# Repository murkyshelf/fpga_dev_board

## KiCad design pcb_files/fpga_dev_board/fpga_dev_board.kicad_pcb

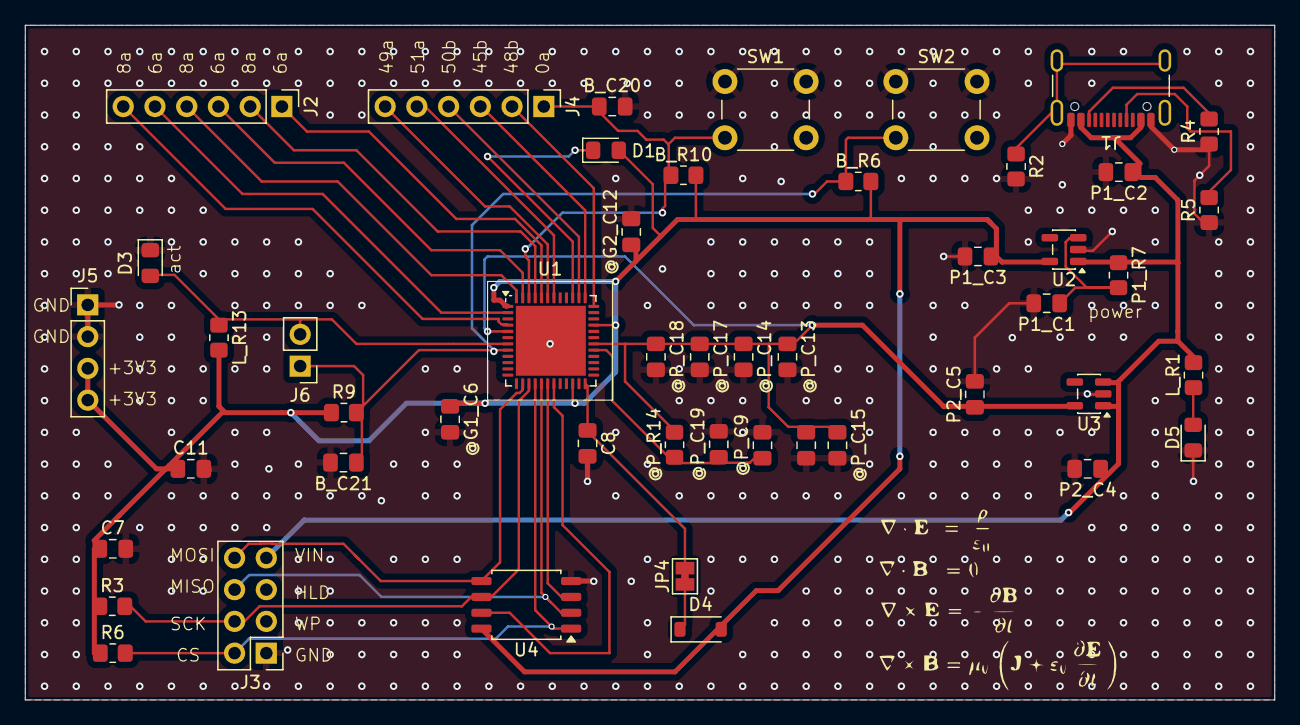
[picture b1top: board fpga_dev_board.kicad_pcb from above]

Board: 2 copper layers, 100.0 x 54.0 mm, 49 parts (0 on the bottom side), 33 nets.

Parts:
@G1_C6, @G2_C12: 100n; C_0805_2012Metric_Pad1.18x1.45mm_HandSolder
@P_C9, @P_C14, @P_C17: 100n; C_0805_2012Metric_Pad1.18x1.45mm_HandSolder
@P_C13, @P_C16: 10n; C_0805_2012Metric_Pad1.18x1.45mm_HandSolder
@P_C15, @P_C18: 1u; C_0805_2012Metric_Pad1.18x1.45mm_HandSolder
@P_C19: 10u; C_0805_2012Metric_Pad1.18x1.45mm_HandSolder
@P_R14: 100E; R_0805_2012Metric_Pad1.20x1.40mm_HandSolder
B_C20, B_C21: 1u; C_0805_2012Metric_Pad1.18x1.45mm_HandSolder
B_R6, B_R10: 10k; R_0805_2012Metric_Pad1.20x1.40mm_HandSolder
C7, C8, C11: 100n; C_0805_2012Metric_Pad1.18x1.45mm_HandSolder
D1: blue; LED_0805_2012Metric_Pad1.15x1.40mm_HandSolder
D3: green; LED_0805_2012Metric_Pad1.15x1.40mm_HandSolder
D4: 1N4148W; D_SOD-123
D5: red; LED_0805_2012Metric_Pad1.15x1.40mm_HandSolder
J1: USB_C; USB_C_Receptacle_GCT_USB4105-xx-A_16P_TopMnt_Horizontal
J2, J4: Conn_01x06; PinHeader_1x06_P2.54mm_Vertical
J3: spi programming; PinHeader_2x04_P2.54mm_Vertical
J5: Conn_01x04; PinHeader_1x04_P2.54mm_Vertical
J6: Conn_01x02; PinHeader_1x02_P2.54mm_Vertical
JP4: Jumper; SolderJumper-2_P1.3mm_Bridged_Pad1.0x1.5mm
L_R1, L_R13: 2k2; R_0805_2012Metric_Pad1.20x1.40mm_HandSolder
P1_C1: 1u; C_0805_2012Metric_Pad1.18x1.45mm_HandSolder
P1_C2, P1_C3, P2_C4, P2_C5: 4u7; C_0805_2012Metric_Pad1.18x1.45mm_HandSolder
P1_R7: 10k; R_0805_2012Metric_Pad1.20x1.40mm_HandSolder
R2: 1M; R_0805_2012Metric_Pad1.20x1.40mm_HandSolder
R3, R6, R9: 10k; R_0805_2012Metric_Pad1.20x1.40mm_HandSolder
R4, R5: 5k1; R_0805_2012Metric_Pad1.20x1.40mm_HandSolder
SW1, SW2: TACT; SW_PUSH_6mm_H5mm
U1: ICE40UP5K-SG48ITR; QFN-48-1EP_7x7mm_P0.5mm_EP5.6x5.6mm
U2, U3: TLV75533PDBV; SOT-23-5
U4: W25Q128JVS; SOIC-8_5.3x5.3mm_P1.27mm

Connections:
+1V2: @P_C13.1, @P_C14.1, @P_C15.1, @P_C16.1, @P_C17.1, @P_C18.1, @P_R14.2, P2_C5.1, U1.5 (VCC), U1.30 (VCC), U3.5 (OUT)
+3V3: @G1_C6.1, @G2_C12.1, B_R6.2, B_R10.2, C7.1, C11.1, D1.2 (A), D4.2 (A), J5.3, J5.4, L_R13.2, P1_C3.1, R3.1, R6.1, R9.1, U1.1 (VCCIO_2), U1.22 (SPI_VCCIO1), U1.33 (VCCIO_0), U2.5 (OUT), U4.8 (VCC)
/CDONE: D3.2 (A), J6.2, L_R13.1, U1.7 (CDONE)
/IOB_0a: B_C20.1, B_R10.1, J4.1, SW1.2, U1.46 (IOB_0a)
/IOB_2a: J2.3, U1.47 (IOB_2a)
/IOB_3a_G6: J2.1, U1.44 (IOB_3b_G6)
/IOB_4a: J2.4, U1.48 (IOB_4a)
/IOB_5a: J2.2, U1.45 (IOB_5b)
/IOB_6a: J2.5, U1.2 (IOB_6a)
/IOB_8a: J2.6, U1.4 (IOB_8a)
/IOT_45b: J4.3, U1.37 (IOT_45a_G1)
/IOT_48b: J4.2, U1.36 (IOT_48b)
/IOT_49a: J4.6, U1.43 (IOT_49a)
/IOT_50b: J4.4, U1.38 (IOT_50b)
/IOT_51a: J4.5, U1.42 (IOT_51a)
/SPI_MISO-IO1: J3.6, U1.17 (IOB_33b_SPI_SI), U4.2 (DO/IO_{1})
/SPI_MOSI-IO0: J3.8, U1.14 (IOB_32a_SPI_SO), U4.5 (DI/IO_{0})
/SPI_SCK: J3.4, R3.2, U1.15 (IOB_34a_SPI_SCK), U4.6 (CLK)
/SPI_~CS: J3.2, R6.2, U1.16 (IOB_35b_SPI_SS), U4.1 (~CS)
/SPI_~HLD-IO3: J3.3, U1.19 (IOB_29b), U4.7 (~HOLD/~RESET/IO_{3})
/SPI_~WP-IO2: J3.5, U1.18 (IOB_31b), U4.3 (~WP/IO_{2})
/led: D1.1 (K), U1.39 (RGB0)
/~BTN: B_C21.1, B_R6.1, J6.1, R9.2, SW2.2, U1.8 (~CRESET)
GND: @G1_C6.2, @G2_C12.2, @P_C9.2, @P_C13.2, @P_C14.2, @P_C15.2, @P_C16.2, @P_C17.2, @P_C18.2, @P_C19.2, B_C20.2, B_C21.2, C7.2, C8.2, C11.2, D3.1 (K), D5.1 (K), J1.A1 (GND), J1.A12 (GND), J1.B1 (GND), J1.B12 (GND), J3.1, J5.1, J5.2, P1_C1.2, P1_C2.2, P1_C3.2, P2_C4.2, P2_C5.2, R2.2, R4.1, R5.1, SW1.1, SW2.1, U1.49 (GND), U2.2 (GND), U3.2 (GND), U4.4 (GND)
unnamed: D4.1 (K), JP4.1 (A)
unnamed: D5.2 (A), L_R1.1
unnamed: J1.A5 (CC1), R5.2
unnamed: J1.B5 (CC2), R4.2
unnamed: J1.S1 (SHIELD), R2.1
unnamed: C8.1, JP4.2 (B), U1.24 (VPP_2V5)
unnamed: @P_C9.1, @P_C19.1, @P_R14.1, U1.29 (VCCPLL)
unnamed: P1_C1.1, P1_R7.2, U2.3 (EN)
VIN: J1.A4 (VBUS), J1.A9 (VBUS), J1.B4 (VBUS), J1.B9 (VBUS), J3.7, L_R1.2, P1_C2.1, P1_R7.1, P2_C4.1, U2.1 (IN), U3.1 (IN), U3.3 (EN)

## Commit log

2026-01-11 added stuff
2026-01-14 fixes in circuit
2026-01-14 update the scamatic
2026-01-14 update the scamatic & pdf
2026-01-17 major changes
2026-01-18 some changes
2026-01-18 updated pdf
2026-01-19 final check ups
2026-01-19 final check ups v0.15
2026-01-19 added pdf v0.1.6
2026-02-15 final change
2026-02-16 add lib
2026-02-16 added Lib
2026-02-16 Ignore KiCad lock files
2026-02-16 Add .lck files to .gitignore
2026-05-02 working prototype
2026-05-02 Remove files not present locally
2026-05-17 report of the FPGA_DEV board
